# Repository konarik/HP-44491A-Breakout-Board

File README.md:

# HP-44491A-Breakout-Board
HP 44491A Breakout Board

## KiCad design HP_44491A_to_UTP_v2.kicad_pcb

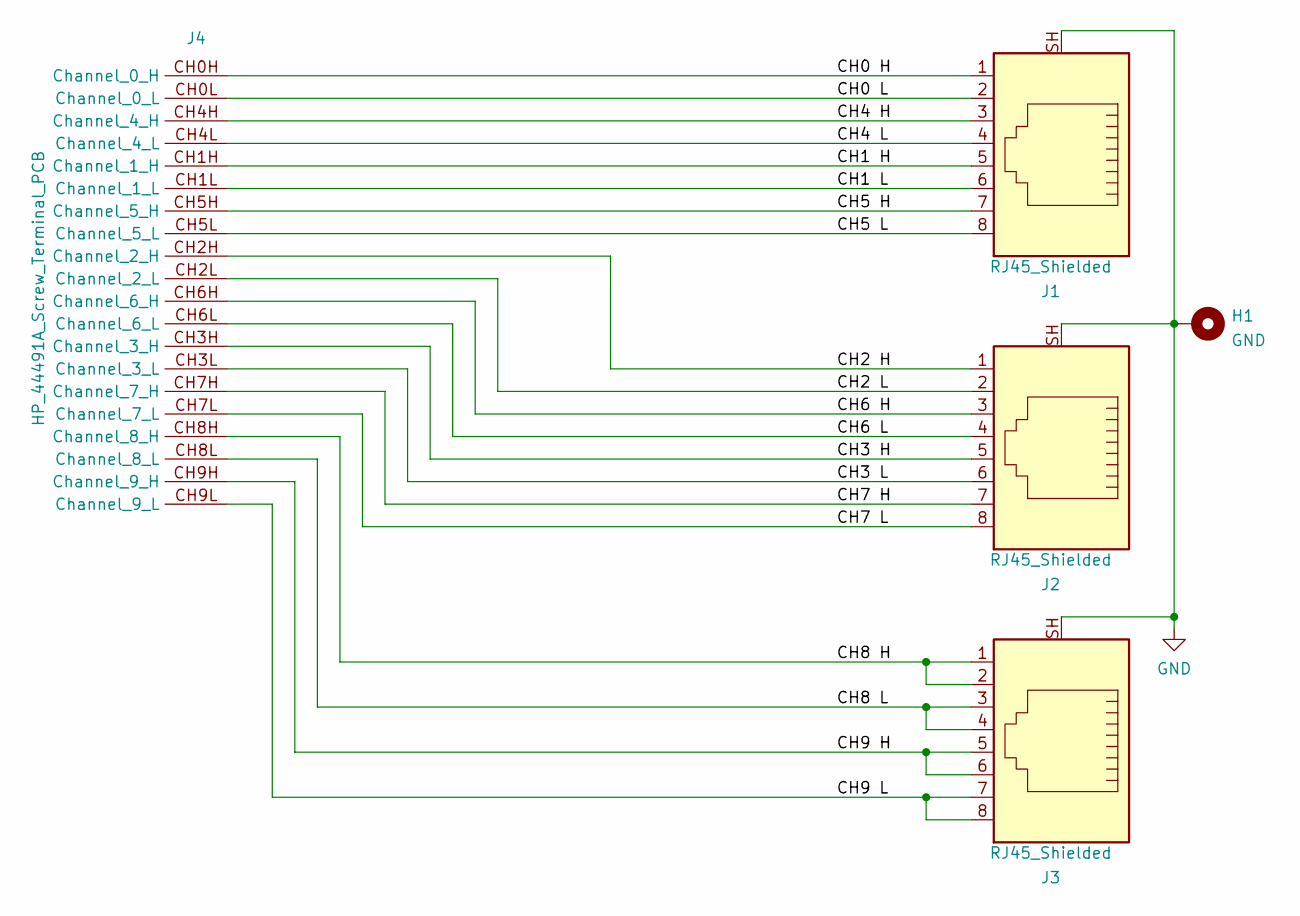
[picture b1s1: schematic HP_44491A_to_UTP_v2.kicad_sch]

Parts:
H1: GND; MountingHole_6.4mm_M6_Pad_Via
J1, J2, J3: RJ45_Shielded; RJ45_OST_PJ012-8P8CX_Vertical_SH
J4: HP_44491A_Screw_Terminal_PCB; 44491A_screw_terminal_PCB

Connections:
/CH0 H: J1.1, J4.CH0H (Channel_0_H)
/CH0 L: J1.2, J4.CH0L (Channel_0_L)
/CH1 H: J1.5, J4.CH1H (Channel_1_H)
/CH1 L: J1.6, J4.CH1L (Channel_1_L)
/CH2 H: J2.1, J4.CH2H (Channel_2_H)
/CH2 L: J2.2, J4.CH2L (Channel_2_L)
/CH3 H: J2.5, J4.CH3H (Channel_3_H)
/CH3 L: J2.6, J4.CH3L (Channel_3_L)
/CH4 H: J1.3, J4.CH4H (Channel_4_H)
/CH4 L: J1.4, J4.CH4L (Channel_4_L)
/CH5 H: J1.7, J4.CH5H (Channel_5_H)
/CH5 L: J1.8, J4.CH5L (Channel_5_L)
/CH6 H: J2.3, J4.CH6H (Channel_6_H)
/CH6 L: J2.4, J4.CH6L (Channel_6_L)
/CH7 H: J2.7, J4.CH7H (Channel_7_H)
/CH7 L: J2.8, J4.CH7L (Channel_7_L)
/CH8 H: J3.1, J3.2, J4.CH8H (Channel_8_H)
/CH8 L: J3.3, J3.4, J4.CH8L (Channel_8_L)
/CH9 H: J3.5, J3.6, J4.CH9H (Channel_9_H)
/CH9 L: J3.7, J3.8, J4.CH9L (Channel_9_L)
GND: H1.1, J1.SH, J2.SH, J3.SH

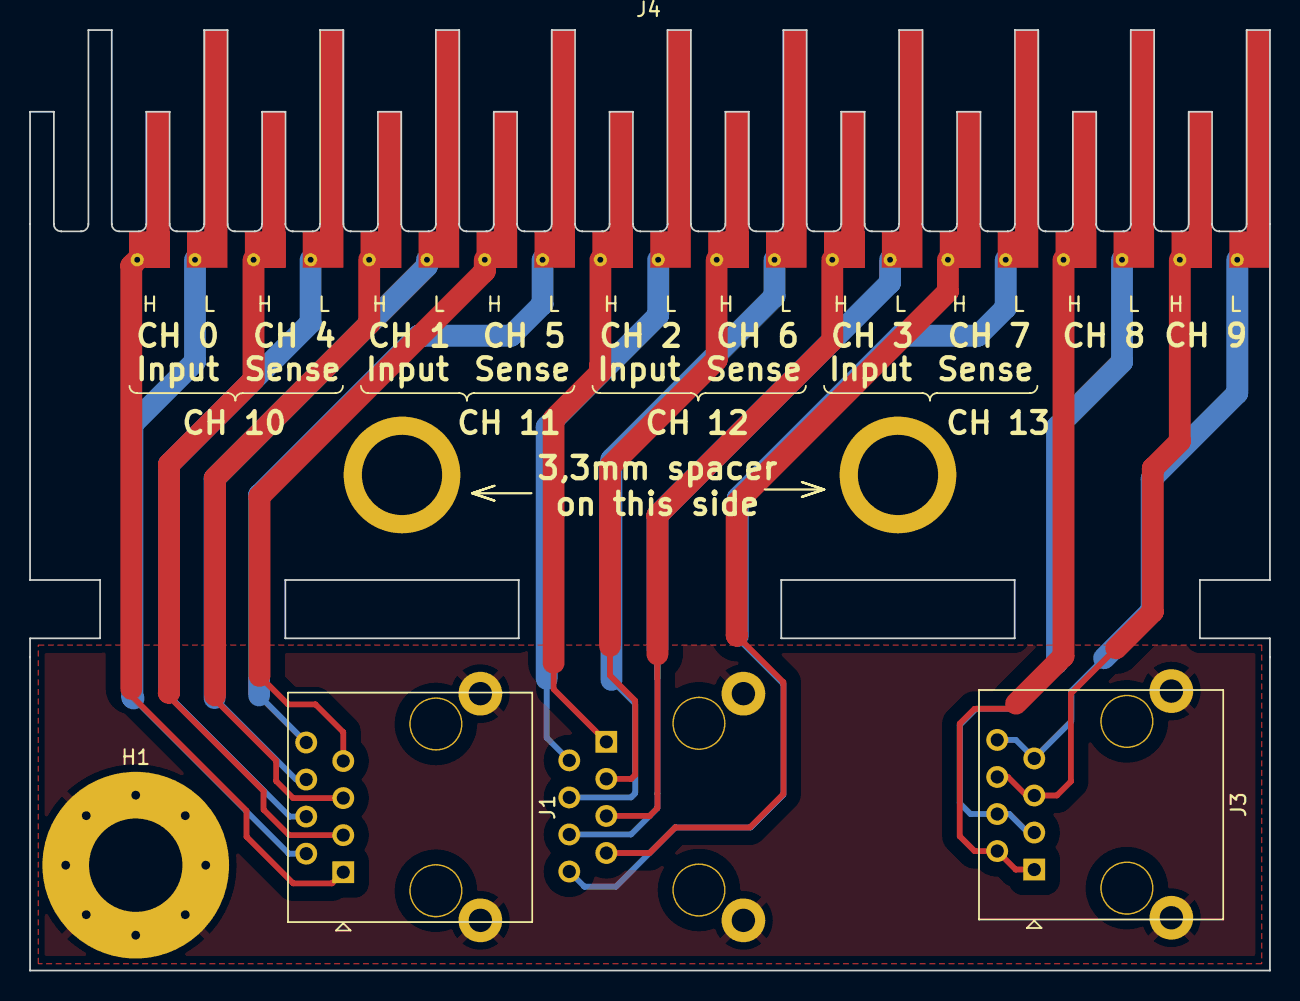
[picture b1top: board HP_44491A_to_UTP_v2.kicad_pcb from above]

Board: 2 copper layers, 85.0 x 64.5 mm, 5 parts (1 on the bottom side), 21 nets.
